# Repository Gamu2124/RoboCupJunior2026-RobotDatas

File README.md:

# AIR - RoboCupJunior2026 RobotData Repository

RoboCupJunior Soccer Lightweight 2026 シーズンにおいて、**ジャパンオープン優勝**、そして世界大会（韓国・仁川）で**競技優勝・総合優勝・コミュニティ賞**を達成したロボット「AIR」の**設計・開発データを公開するリポジトリ**です。

This repository contains the **design, hardware, and software data of AIR**, the **RoboCupJunior Soccer Lightweight 2026 Japan Open Champion and World Championship Champion**.

---
# 概要 / Overview

本リポジトリは、**次世代のRCJコミュニティおよび学生ロボティクスエンジニアへの情報共有**を目的として公開されています。

2026シーズンの開発で使用した**回路設計、組み込みソフトウェア、マルチマイコンによる分散処理システム、3D CADデータ**など、AIRのロボット開発に関する設計データを公開しています。

We open-source **AIR's robot design and development data** to support the global RCJ community and future student roboticists.

The repository includes **custom PCB designs, multi-MCU embedded firmware, and 3D CAD models** used in the development of AIR during the 2026 season.

---

<table align="center">
  <tr>
    <td align="center">
      
      <br>
      <b>Japan Open 2026</b>
    </td>
    <td align="center">
      
      <br>
      <b>World Championship 2026</b>
    </td>
  </tr>
</table>

---

# 大会実績 / Competition Results

* **RoboCupJunior Japan Open 2026**

  * 🥇 **競技 優勝 / 1st Place**

* **RoboCup World Championship 2026**

  * **Incheon, Republic of Korea**
  * 🥇 **競技 優勝 / Individual 1st Place**
  * 🏆 **総合 優勝 / Overall 1st Place**
  * 🏅 **コミュニティ賞 / Community Award**

---

# 技術的ハイライト / Technical Highlights

AIRのシステムは、**高速なセンサ処理と制御、複数のマイコンへの処理分散、そして競技環境での安定動作**を重視して設計されています。

* **Teensy 4.1を中心としたマルチマイコン分散処理**

  メインマイコンとして**Teensy 4.1**を使用し、複数のUARTを介してボール検出、ライン検出、壁面距離計測、UIなどの処理をサブマイコンへ分散しています。

* **24基のTSSP58038による高密度ボール検出**

  **RP2350Aと24個の赤外線センサ**を使用し、複数方向からのボール検出を高速に行います。得られたセンサ情報から**ボールの方向や距離を推定**し、ロボットの走行制御に利用しています。

* **FreeRTOSを用いた非ブロッキング超音波計測**

  **XIAO ESP32-S3上でFreeRTOSを利用**し、超音波センサによる壁面距離計測をメインの制御処理から分離しています。

* **電源・回路の安定性を重視した設計**

  **DCDCコンバータによる電源系統の分離**、大電流を扱うキッカー回路、複数のマイコン・センサ・モータドライバを統合した電源および信号系統を設計しています。

* **世界大会でのリモートシステムへの対応**

  **世界大会で使用された公式リモートシステム**に対応するための通信・制御機能を実装しています。

---

# リポジトリ構成 / Repository Structure

```text
.
├── Circuit/             # 回路・PCB設計データ (KiCad)
├── Hardware/            # 3D CAD・機械設計データ
├── Program/             # 組み込みソフトウェア・プログラム
├── PresentationSheet/   # プレゼンテーション・資料
├── .gitattributes
└── README.md
```

---

# ハードウェア仕様とシステム進化 / Hardware Architecture & Evolution

AIRのハードウェア構成は、**ジャパンオープンから世界大会（Incheon）にかけて大幅に進化**しました。

| ユニット / System              | Japan Open モデル                    | World Championship (Incheon) モデル |
| -------------------------- | --------------------------------- | -------------------------------- |
| **Main MCU**               | Teensy 4.1                        | Teensy 4.1                       |
| **Ball Sub MCU & Sensors** | ATmega32U4 + TSSP4038             | **RP2350A + TSSP58038 × 24**     |
| **Line Sub MCU & Sensors** | ATmega2560 + B19H1LS / LM393      | **RP2350B + B19H1LS / LM393**    |
| **Wall / US MCU**          | XIAO ESP32-S3                     | XIAO ESP32-S3                    |
| **UI & Remote Control**    | ESP32 WROOM-32E + OLED + NeoPixel | **XIAO ESP32-S3 + OLED**         |
| **Motor Driver**           | DRV8432                           | **DRV8432**                      |
| **Kicker System**          | CB1037 + Pch/Nch MOSFET           | **CB1037 + AQW212 + XL6009**     |
| **Power Distribution**     | LM2576系電源                         | **AP64500SP系電源**                 |

---

# ソフトウェア機能 / Software Architecture

主に**C/C++およびPython**を用いて開発された、**マルチマイコン分散処理によるロボット制御システム**です。

* **Ball Tracking**

  **24個のTSSP58038**から得られるセンサ情報をRP2350Aで高速処理し、**ボールの方向および距離を推定**します。

* **Line Keep**

  **B19H1LSおよびLM393**を使用したラインセンサシステムにより、フィールド上の白線を検出し、フィールド外への逸脱を防止します。

* **Wall Distance**

  ESP32-S3上で**FreeRTOS**を利用し、超音波センサによる壁面距離計測をバックグラウンドで実行します。

* **Motion Control**

  **IMU（BNO055）から得られる姿勢情報を利用したPIDベースの全方向移動制御**を行います。

* **Strategy State Machine**

  ボール検出、ライン検出、壁面距離、ロボットの状態などの情報をもとに、**試合中の動作を状態機械として制御**します。

* **World Championship Remote Control**

  **世界大会で使用された公式リモートシステムに対応した通信・制御機能**を実装しています。

---

# 開発環境・使用設備 / Development Environment & Equipment

### Software Tools

* **3D CAD**: Autodesk Fusion 360
* **EDA (PCB Design)**: KiCad
* **IDE / Programming**: Visual Studio Code / MaixPy IDE
* **Presentation & Media**: Canva

### Hardware & Manufacturing Equipment

* **3D Printers**: Bambu Lab A1 mini / Bambu Lab P1S / Flashforge Adventurer 5M
* **PCB Fabrication**: JLCPCB
* **Machining / Tools**: 小型CNC加工機

---

# CAD設計データ / CAD Models

AIRを構成する**カスタム機械部品をAutodesk Fusion 360で設計**しています。

主な設計データには以下が含まれます。

* **シャーシ構造** / Chassis
* **キッカーユニット** / Kicker Unit
* **センサマウント各種** / Sensor Mounts
* **オムニホイールモジュール** / Omni Wheel Modules
* **ドリブラー機構** / Dribbler Mechanism

---

# 公開基板データ / PCB Designs

ロボットに使用した**自作基板のKiCad設計データ**を公開しています。

## 日本大会機

1. **メイン基板 (`main_unit`)**
   各種マイコン・センサ・制御系を統合したメイン基板

2. **ボールセンサー基板 (`ball_unit`)**
   **TSSP4038およびATmega32U4**を搭載したボール検出基板

3. **ラインセンサー基板 (`line_unit`)**
   **B19H1LS、LM393、ATmega2560**を搭載したライン検出基板

4. **電源基板 (`power_unit`)**
   **LM2576**を使用した電源基板

5. **モータドライバ基板 (`md_unit`)**
   **DRV8432**を使用したモータドライバ基板

6. **キッカー制御基板 (`kicker_unit`)**
   キッカー用の**大電流スイッチング・絶縁回路**

## 世界大会機

1. **メイン基板 (`main_unit`)**
   各種マイコン・IMU・UIなどを統合したメイン基板

2. **ボールセンサー基板 (`ball_unit`)**
   **TSSP58038 × 24およびRP2350A**を搭載した高密度ボール検出基板

3. **ラインセンサー基板 (`line_unit`)**
   **B19H1LS、LM393、RP2350B**を搭載したライン検出基板

4. **電源基板 (`power_unit`)**
   **AP64500SP**を使用した電源基板

5. **モータドライバ基板 (`md_unit`)**
   **DRV8432**を使用したモータドライバ基板

6. **キッカー制御基板 (`kicker_unit`)**
   **昇圧回路、大電流スイッチング回路、AQW212**を使用したキッカー制御基板

---

# スポンサー / Sponsors

本プロジェクトの活動を支援していただいたスポンサー・団体の皆様に、心より感謝申し上げます。

* **JLCPCB**
  https://jlcpcb.com/

* **DigiKey**
  https://www.digikey.jp/

* **株式会社人機一体**
  https://www.jinki.jp/

* **MAXON**
  https://maxonjapan.com/

* **タカハ機工株式会社**
  https://www.takaha.co.jp/

* **株式会社システムアイインターナショナル**
  https://www.systemi.com/

* **ライフ&キャリアコンサルティング LACIQUE**
  https://www.lacique.com/

* **医療法人社団 翠会 水口病院**
  https://www.minakuchi-hp.or.jp/

* **JOJISTABLE**
  https://x.com/JojiStable

* **立命館守山高校 & 立命館大学**
  https://www.mrc.ritsumei.ac.jp/
  https://www.ritsumei.ac.jp/

---

# チーム情報・お問い合わせ / Team Information & Contact

## AIR

**RoboCupJunior Soccer Lightweight & Infrared Team from Japan**

**World Champion 2026**

### チーム実績 / Team History

* **2025 シーズン**

  * RoboCupJunior Japan Open 2025 🥉 **3位**
  * RoboCup World Championship 2025
    Salvador, Brazil 🥉 **Individual 3rd Place**

* **2026 シーズン**

  * RoboCupJunior Japan Open 2026 🥇 **優勝**
  * RoboCup World Championship 2026
    Incheon, Republic of Korea 🏆 **Individual 1st Place**
  * 🏅 **Community Award**

---

### お問い合わせ・ご質問 / Contact Information

本リポジトリの内容、設計データ、その他技術的なご質問やお問い合わせについては、以下よりご連絡ください。

* **X (Twitter) DM**: [@Air_Gamu_rcj](https://x.com/Air_Gamu_rcj)

* **Email**: [airkorea2026@gmail.com](mailto:airkorea2026@gmail.com)

### 公式メディア・SNS / Links

* **X (Twitter)**: [@Air_3838](https://x.com/Air_3838)

* **YouTube**: [AIR-RCJ Channel](https://www.youtube.com/@AIR-RCJ)

* **note**: [AIR Official note](https://note.com/air_rcj)

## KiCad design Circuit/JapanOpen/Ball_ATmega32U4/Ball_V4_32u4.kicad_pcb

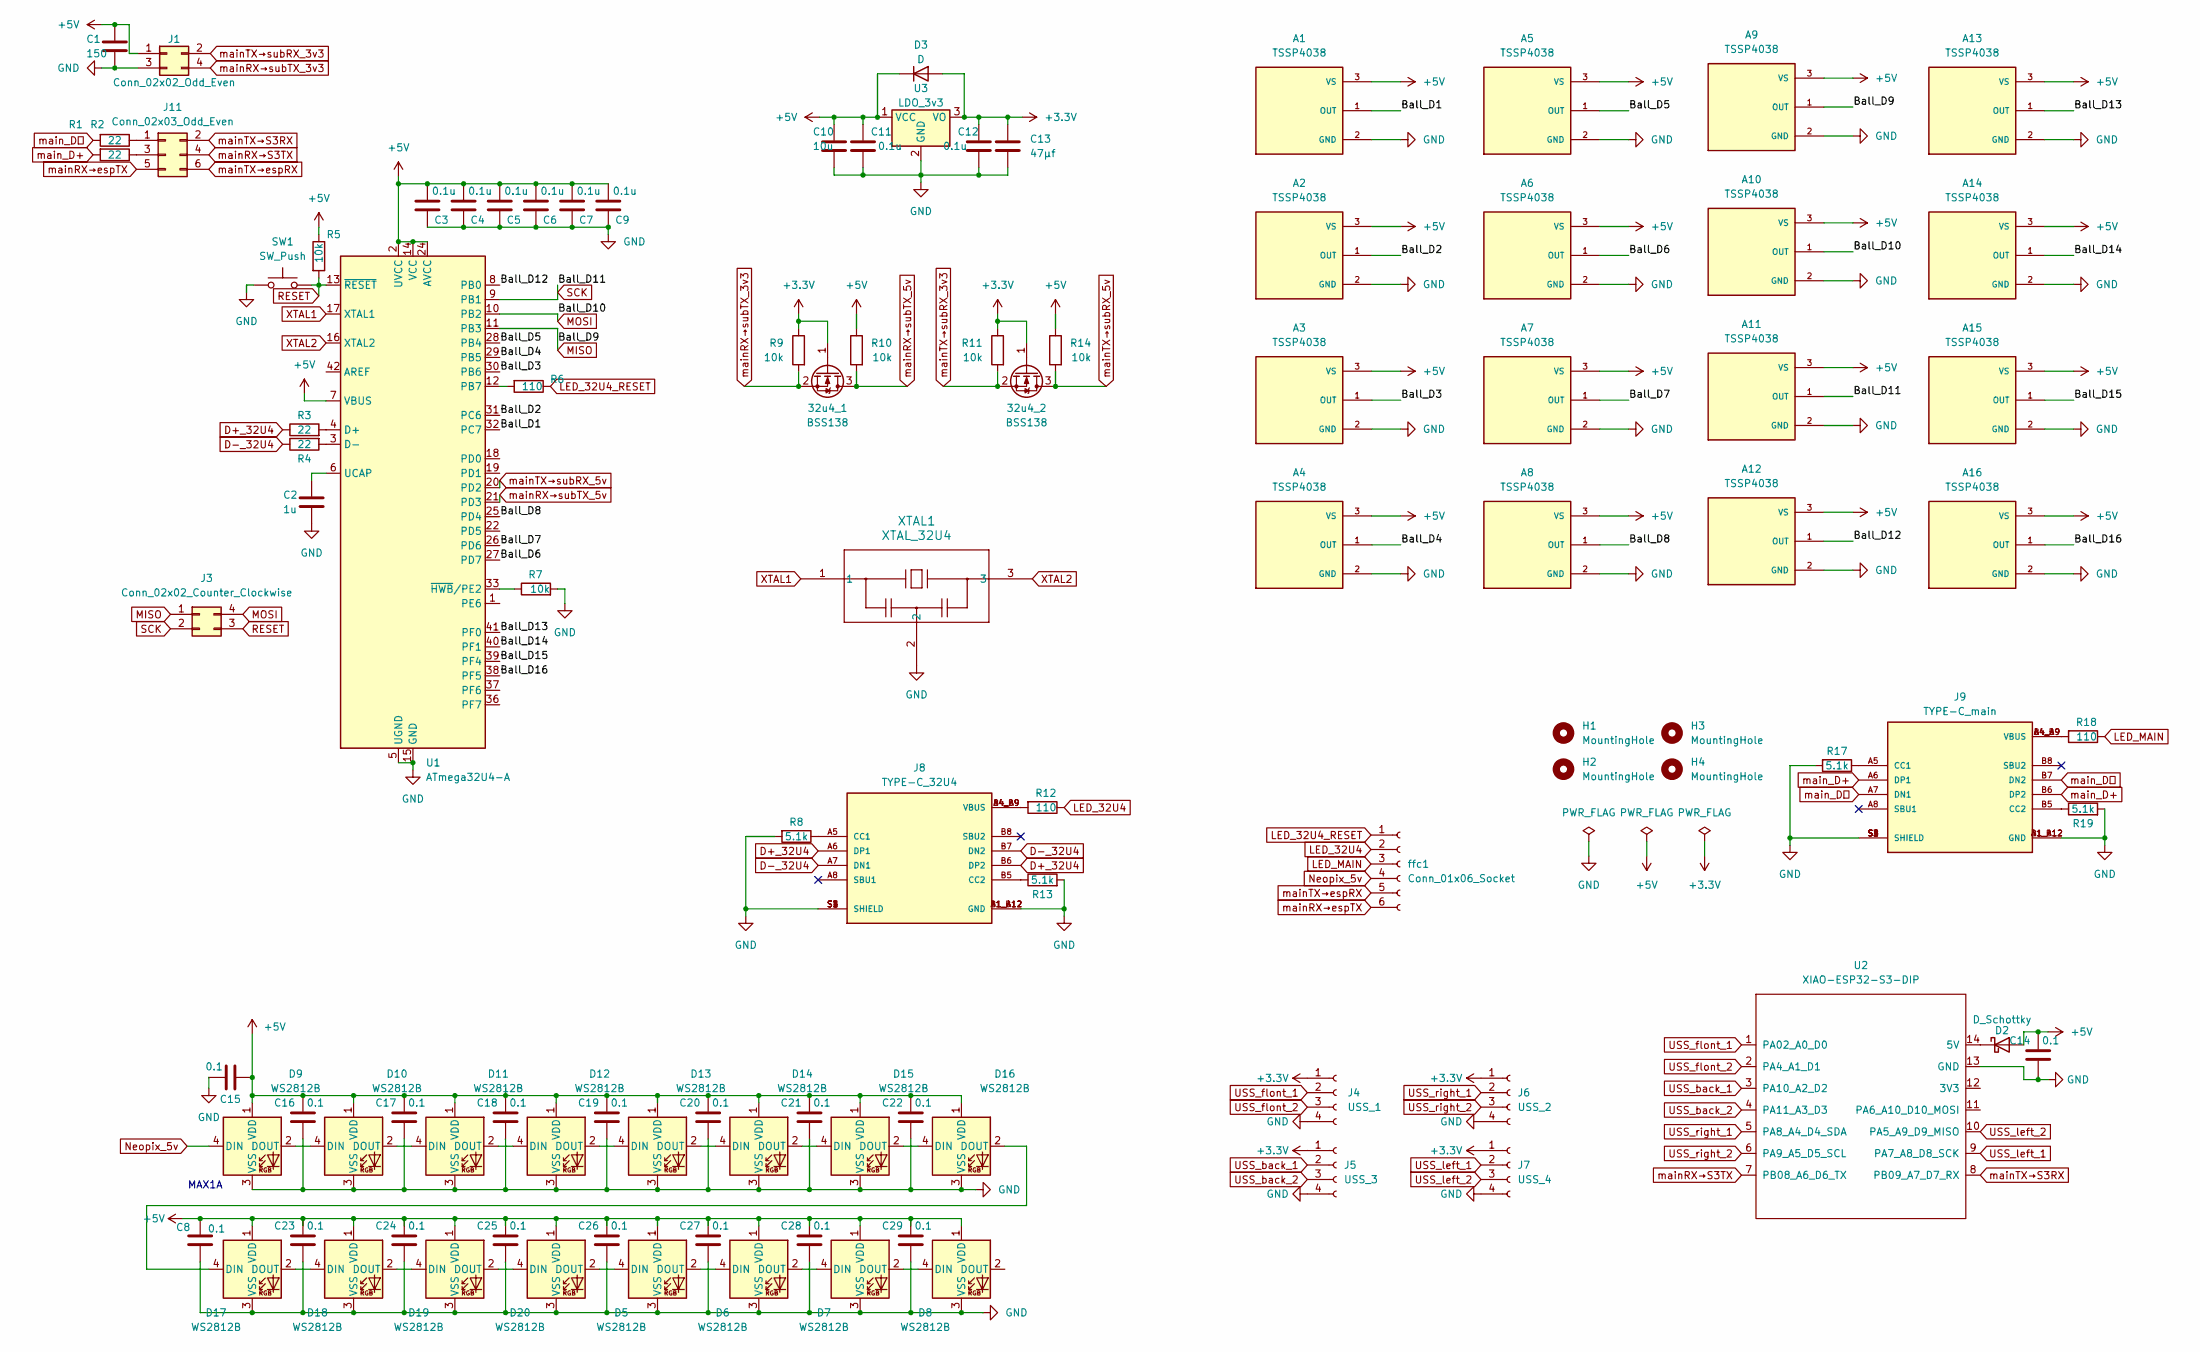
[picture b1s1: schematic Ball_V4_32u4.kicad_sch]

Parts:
32u4_1, 32u4_2: BSS138; SOT-23; LCSC C192057
A1, A2, A3, A4, A5, A6, A7, A8, A9, A10, A11, A12, A13, A14, A15, A16: TSSP4038; XDCR_TSSP4038; PARTREV 2.3
C1: 150; CP_Radial_D5.0mm_P2.50mm; LCSC C59923
C2: 1u; C_1206_3216Metric; LCSC C1848
C3, C4, C5, C6, C7, C9, C11, C12: 0.1u; C_0603_1608Metric_Pad1.08x0.95mm_HandSolder; LCSC C1581
C8, C14, C16, C17, C18, C19, C20, C21, C22, C23, C24, C25, C26, C27, C28, C29: 0.1; C_0603_1608Metric_Pad1.08x0.95mm_HandSolder; LCSC C1581
C10: 10u; C_0805_2012Metric; LCSC C1713
C13: 47μf; CP_Radial_D5.0mm_P2.00mm
C15: 0.1; C_0603_1608Metric_Pad1.08x0.95mm_HandSolder; LCSC C1848
D2: D_Schottky; D_A-405_P10.16mm_Horizontal
D3: D; D_SOD-123F
D5, D6, D7, D8, D9, D10, D11, D12, D13, D14, D15, D16, D17, D18, D19, D20: WS2812B; LED_WS2812B_PLCC4_5.0x5.0mm_P3.2mm
H1, H2, H3, H4: MountingHole; MountingHole_3.2mm_M3
J1: Conn_02x02_Odd_Even; PinHeader_2x02_P2.54mm_Vertical
J3: Conn_02x02_Counter_Clockwise; PinHeader_2x02_P2.54mm_Vertical
J4: USS_1; PinSocket_1x04_P2.54mm_Vertical
J5: USS_3; PinSocket_1x04_P2.54mm_Vertical
J6: USS_2; PinSocket_1x04_P2.54mm_Vertical
J7: USS_4; PinSocket_1x04_P2.54mm_Vertical
J8: TYPE-C_32U4; NELTRON_5077CR-16SMC2-BK-TR; PARTREV B
J9: TYPE-C_main; NELTRON_5077CR-16SMC2-BK-TR; PARTREV B
J11: Conn_02x03_Odd_Even; PinSocket_2x03_P2.54mm_Vertical
R1, R2, R3, R4: 22; R_1206_3216Metric; LCSC C17958
R5, R7, R9, R10, R11, R14: 10k; R_1206_3216Metric; LCSC C1489
R6, R12, R18: 110; R_1206_3216Metric; LCSC C17909
R8, R13, R17, R19: 5.1k; R_0603_1608Metric_Pad0.98x0.95mm_HandSolder; LCSC C26033
SW1: SW_Push; Switch_SKRPABE010
U1: ATmega32U4-A; TQFP-44_10x10mm_P0.8mm; LCSC C44854
U2: XIAO-ESP32-S3-DIP; XIAO-ESP32-S3-SMD
U3: LDO_3v3; TO-252-2
XTAL1: XTAL_32U4; CSTNE16M0V530000R0_MUR
ffc1: Conn_01x06_Socket; TE_84952-6_1x06-1MP_P1.0mm_Horizontal

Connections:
+3.3V: 32u4_1.1 (G), 32u4_2.1 (G), C12.1, C13.1, D3.2 (A), J4.1, J5.1, J6.1, J7.1, R9.1, R11.1, U3.3 (VO)
+5V: A1.3 (VS), A2.3 (VS), A3.3 (VS), A4.3 (VS), A5.3 (VS), A6.3 (VS), A7.3 (VS), A8.3 (VS), A9.3 (VS), A10.3 (VS), A11.3 (VS), A12.3 (VS), A13.3 (VS), A14.3 (VS), A15.3 (VS), A16.3 (VS), C1.1, C3.2, C4.2, C5.2, C6.2, C7.2, C8.2, C9.2, C10.1, C11.1, C14.2, C15.2, C16.2, C17.2, C18.2, C19.2, C20.2, C21.2, C22.2, C23.2, C24.2, C25.2, C26.2, C27.2, C28.2, C29.2, D2.2 (A), D3.1 (K), D5.1 (VDD), D6.1 (VDD), D7.1 (VDD), D8.1 (VDD), D9.1 (VDD), D10.1 (VDD), D11.1 (VDD), D12.1 (VDD), D13.1 (VDD), D14.1 (VDD), D15.1 (VDD), D16.1 (VDD), D17.1 (VDD), D18.1 (VDD), D19.1 (VDD), D20.1 (VDD), J1.1, R5.1, R10.1, R14.1, U1.2 (UVCC), U1.7 (VBUS), U1.14 (VCC), U1.24 (AVCC), U1.34 (VCC), U1.44 (AVCC), U3.1 (VCC)
/Ball_D1: A1.1 (OUT), U1.32 (PC7)
/Ball_D2: A2.1 (OUT), U1.31 (PC6)
/Ball_D3: A3.1 (OUT), U1.30 (PB6)
/Ball_D4: A4.1 (OUT), U1.29 (PB5)
/Ball_D5: A5.1 (OUT), U1.28 (PB4)
/Ball_D6: A6.1 (OUT), U1.27 (PD7)
/Ball_D7: A7.1 (OUT), U1.26 (PD6)
/Ball_D8: A8.1 (OUT), U1.25 (PD4)
/Ball_D12: A12.1 (OUT), U1.8 (PB0)
/Ball_D13: A13.1 (OUT), U1.41 (PF0)
/Ball_D14: A14.1 (OUT), U1.40 (PF1)
/Ball_D15: A15.1 (OUT), U1.39 (PF4)
/Ball_D16: A16.1 (OUT), U1.38 (PF5)
D+_32U4: J8.A6 (DP1), J8.B6 (DP2), R3.1
D-_32U4: J8.A7 (DN1), J8.B7 (DN2), R4.1
GND: A1.2 (GND), A2.2 (GND), A3.2 (GND), A4.2 (GND), A5.2 (GND), A6.2 (GND), A7.2 (GND), A8.2 (GND), A9.2 (GND), A10.2 (GND), A11.2 (GND), A12.2 (GND), A13.2 (GND), A14.2 (GND), A15.2 (GND), A16.2 (GND), C1.2, C2.2, C3.1, C4.1, C5.1, C6.1, C7.1, C8.1, C9.1, C10.2, C11.2, C12.2, C13.2, C14.1, C15.1, C16.1, C17.1, C18.1, C19.1, C20.1, C21.1, C22.1, C23.1, C24.1, C25.1, C26.1, C27.1, C28.1, C29.1, D5.3 (VSS), D6.3 (VSS), D7.3 (VSS), D8.3 (VSS), D9.3 (VSS), D10.3 (VSS), D11.3 (VSS), D12.3 (VSS), D13.3 (VSS), D14.3 (VSS), D15.3 (VSS), D16.3 (VSS), D17.3 (VSS), D18.3 (VSS), D19.3 (VSS), D20.3 (VSS), J1.3, J4.4, J5.4, J6.4, J7.4, J8.A1_B12 (GND), J8.B1_A12 (GND), J8.S1 (SHIELD), J8.S2 (SHIELD), J8.S3 (SHIELD), J8.S4 (SHIELD), J9.A1_B12 (GND), J9.B1_A12 (GND), J9.S1 (SHIELD), J9.S2 (SHIELD), J9.S3 (SHIELD), J9.S4 (SHIELD), R7.2, R8.2, R13.2, R17.2, R19.2, SW1.2, U1.5 (UGND), U1.15 (GND), U1.23 (GND), U1.35 (GND), U1.43 (GND), U2.13 (GND), U3.2 (GND), XTAL1.2
LED_32U4: R12.1, ffc1.2
LED_32U4_RESET: R6.1, ffc1.1
LED_MAIN: R18.1, ffc1.3
MISO: A9.1 (OUT), J3.1, U1.11 (PB3)
MOSI: A10.1 (OUT), J3.4, U1.10 (PB2)
Neopix_5v: D9.4 (DIN), ffc1.4
unnamed: D2.1 (K), U2.14 (5V)
unnamed: D5.2 (DOUT), D6.4 (DIN)
unnamed: D6.2 (DOUT), D7.4 (DIN)
unnamed: D7.2 (DOUT), D8.4 (DIN)
unnamed: D9.2 (DOUT), D10.4 (DIN)
unnamed: D10.2 (DOUT), D11.4 (DIN)
unnamed: D11.2 (DOUT), D12.4 (DIN)
unnamed: D12.2 (DOUT), D13.4 (DIN)
unnamed: D13.2 (DOUT), D14.4 (DIN)
unnamed: D14.2 (DOUT), D15.4 (DIN)
unnamed: D15.2 (DOUT), D16.4 (DIN)
unnamed: D16.2 (DOUT), D17.4 (DIN)
unnamed: D17.2 (DOUT), D18.4 (DIN)
unnamed: D18.2 (DOUT), D19.4 (DIN)
unnamed: D19.2 (DOUT), D20.4 (DIN)
unnamed: D5.4 (DIN), D20.2 (DOUT)
unnamed: J8.A5 (CC1), R8.1
unnamed: J8.B5 (CC2), R13.1
unnamed: J8.A4_B9 (VBUS), J8.B4_A9 (VBUS), R12.2
unnamed: J9.A5 (CC1), R17.1
unnamed: J9.B5 (CC2), R19.1
unnamed: J9.A4_B9 (VBUS), J9.B4_A9 (VBUS), R18.2
unnamed: J11.1, R1.1
unnamed: J11.3, R2.1
unnamed: R3.2, U1.4 (D+)
unnamed: R4.2, U1.3 (D-)
unnamed: R6.2, U1.12 (PB7)
unnamed: C2.1, U1.6 (UCAP)
unnamed: R7.1, U1.33 (~HWB/PE2)
RESET: J3.3, R5.2, SW1.1, U1.13 (~RESET)
SCK: A11.1 (OUT), J3.2, U1.9 (PB1)
USS_back_1: J5.2, U2.3 (PA10_A2_D2)
USS_back_2: J5.3, U2.4 (PA11_A3_D3)
USS_flont_1: J4.2, U2.1 (PA02_A0_D0)
USS_flont_2: J4.3, U2.2 (PA4_A1_D1)
USS_left_1: J7.2, U2.9 (PA7_A8_D8_SCK)
USS_left_2: J7.3, U2.10 (PA5_A9_D9_MISO)
USS_right_1: J6.2, U2.5 (PA8_A4_D4_SDA)
USS_right_2: J6.3, U2.6 (PA9_A5_D5_SCL)
XTAL1: U1.17 (XTAL1), XTAL1.1
XTAL2: U1.16 (XTAL2), XTAL1.3
mainRX→S3TX: J11.4, U2.7 (PB08_A6_D6_TX)
mainRX→espTX: J11.5, ffc1.6
mainRX→subTX_3v3: 32u4_1.2 (S), J1.4, R9.2
mainRX→subTX_5v: 32u4_1.3 (D), R10.2, U1.21 (PD3)
mainTX→S3RX: J11.2, U2.8 (PB09_A7_D7_RX)
mainTX→espRX: J11.6, ffc1.5
mainTX→subRX_3v3: 32u4_2.2 (S), J1.2, R11.2
mainTX→subRX_5v: 32u4_2.3 (D), R14.2, U1.20 (PD2)
main_D+: J9.A6 (DP1), J9.B6 (DP2), R2.2
main_Dー: J9.A7 (DN1), J9.B7 (DN2), R1.2

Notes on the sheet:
MAX1A

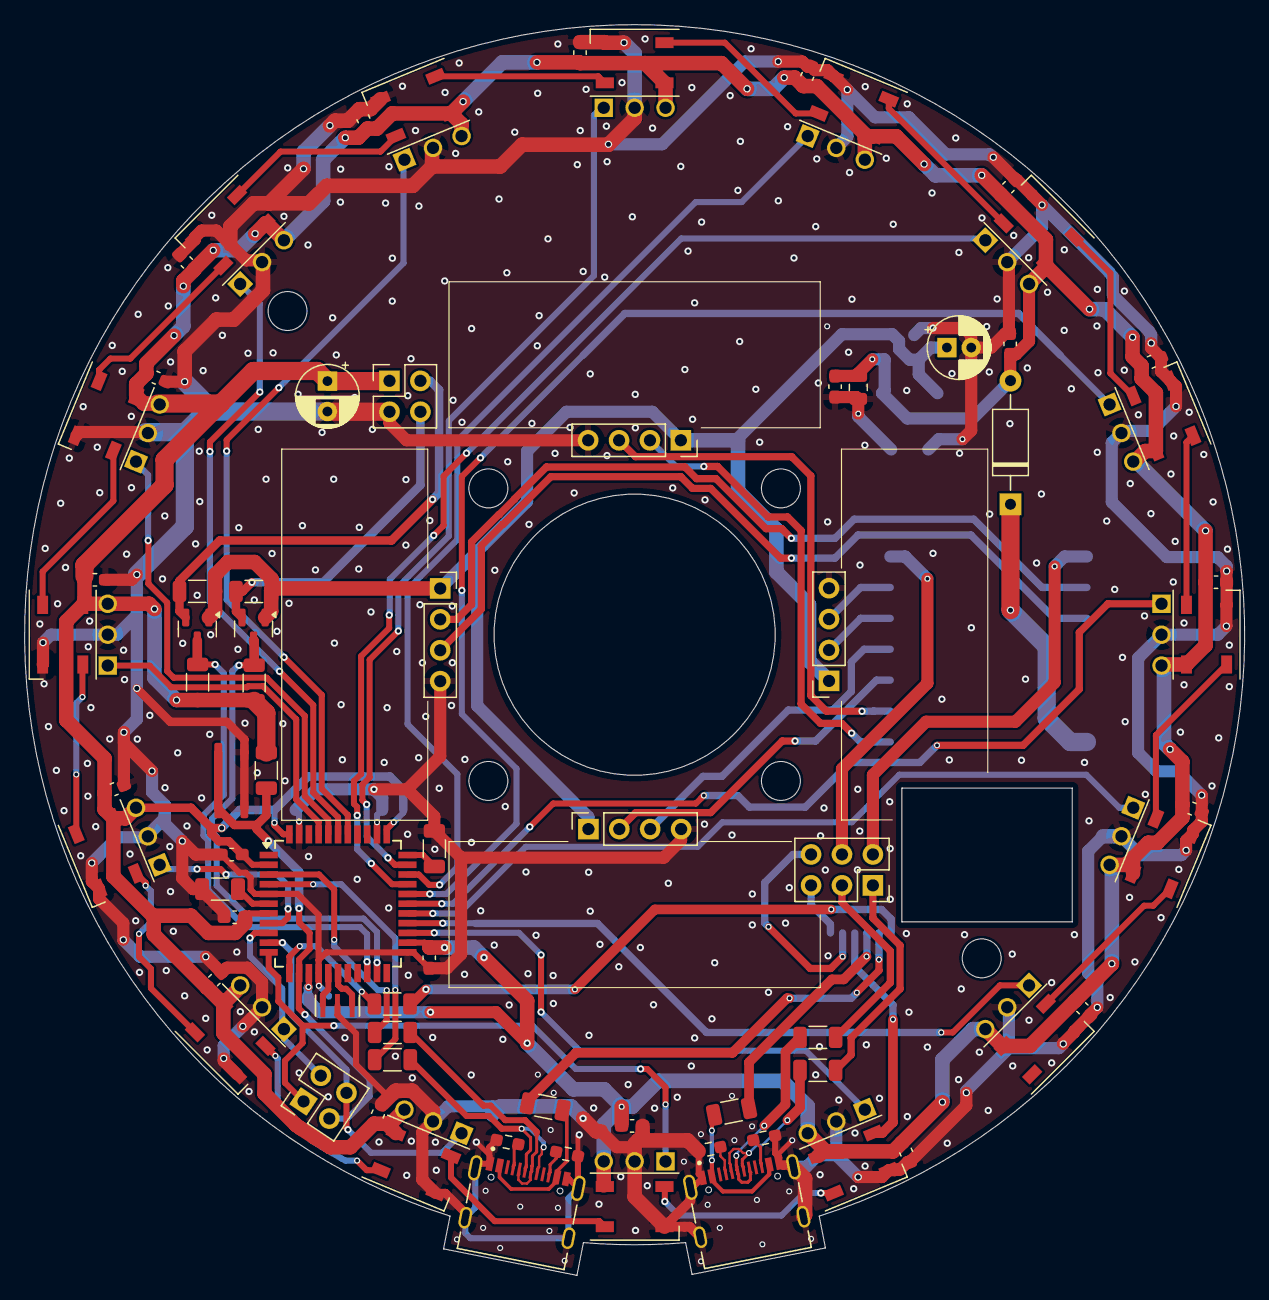
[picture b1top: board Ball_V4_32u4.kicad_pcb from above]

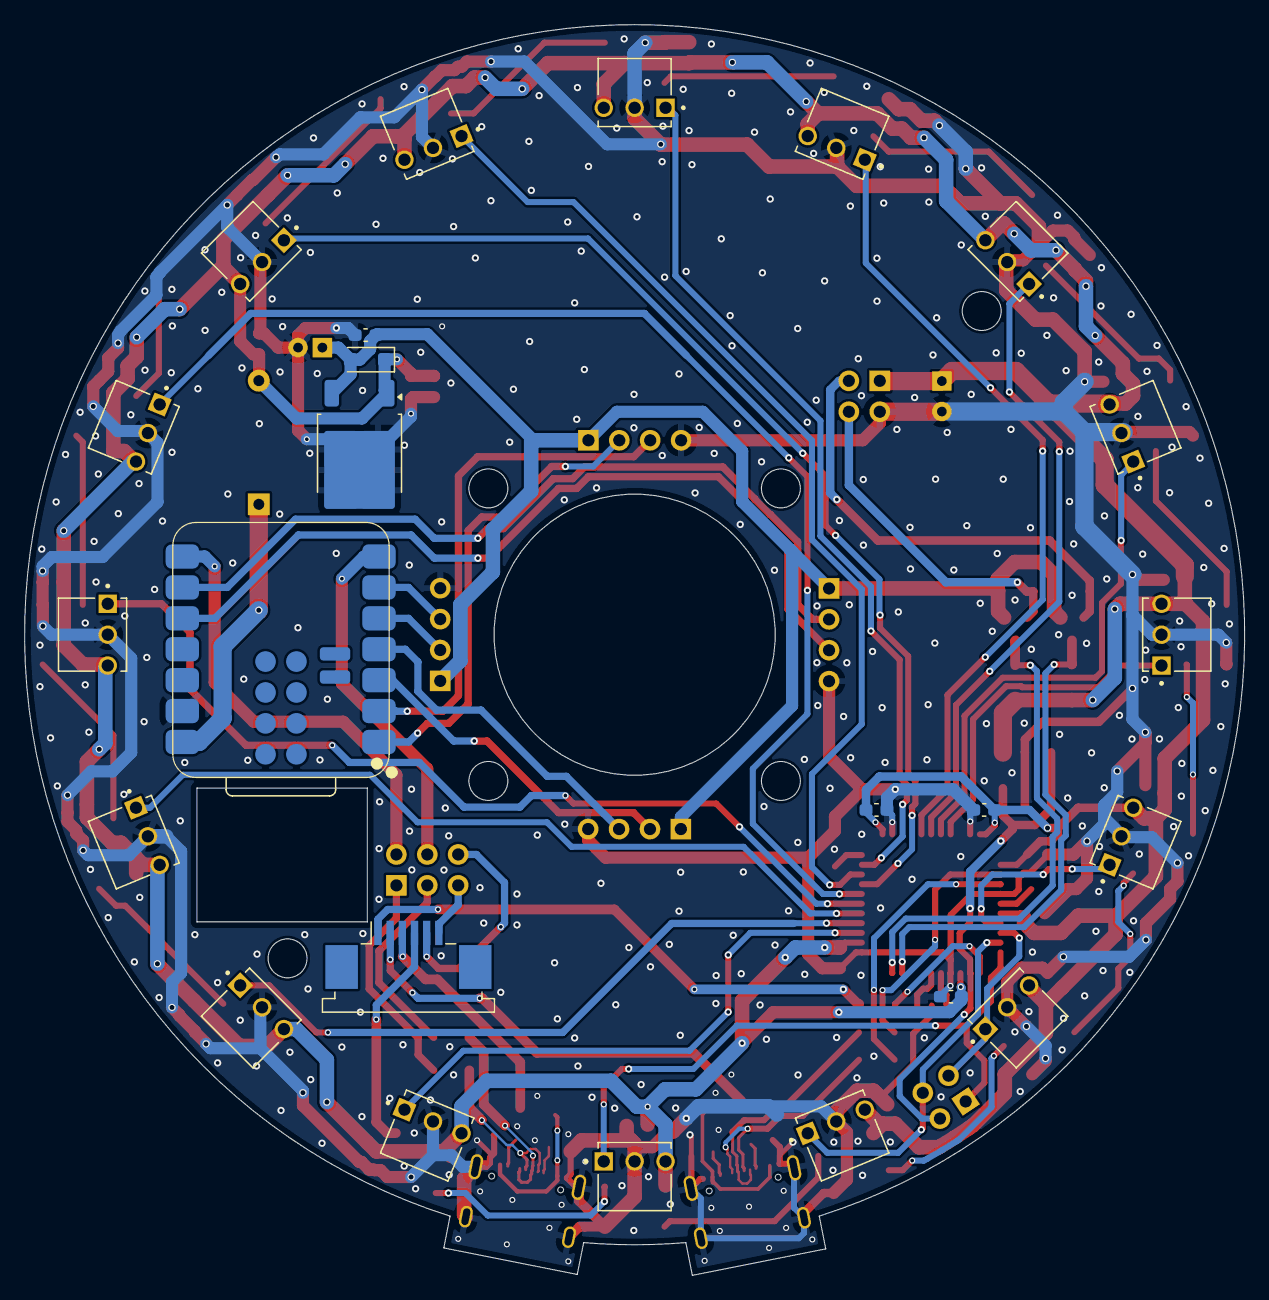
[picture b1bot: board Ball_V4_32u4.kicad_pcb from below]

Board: 2 copper layers, 100.3 x 102.8 mm, 103 parts (24 on the bottom side), 75 nets.

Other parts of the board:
H5, H5#2: MountingHole; MountingHole_3.2mm_M3

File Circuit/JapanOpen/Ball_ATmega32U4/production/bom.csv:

Designator,Footprint,Quantity,Value,LCSC Part #
"32U4_1, 32U4_2",SOT-23,2,BSS138, C192057
"A1, A10, A11, A12, A13, A14, A15, A16, A2, A3, A4, A5, A6, A7, A8, A9",XDCR_TSSP4038,16,TSSP4038,
C1,CP_Radial_D5.0mm_P2.50mm,1,150,C59923
C10,0805,1,10u, C1713
"C11, C12, C3, C4, C5, C6, C7, C9",0603,8,0.1u,C1581
C13,CP_Radial_D5.0mm_P2.00mm,1,47μf,
"C14, C16, C17, C18, C19, C20, C21, C22, C23, C24, C25, C26, C27, C28, C29, C8",0603,16,0.1,C1581
C15,0603,1,0.1,C1848 
C2,1206,1,1u,C1848 
"D10, D11, D12, D13, D14, D15, D16, D17, D18, D19, D20, D5, D6, D7, D8, D9",LED_WS2812B_PLCC4_5.0x5.0mm_P3.2mm,16,WS2812B,
D2,D_A-405_P10.16mm_Horizontal,1,D_Schottky,
D3,D_SOD-123F,1,D,
FFC1,TE_84952-6_1x06-1MP_P1.0mm_Horizontal,1,Conn_01x06_Socket,
J1,PinHeader_2x02_P2.54mm_Vertical,1,Conn_02x02_Odd_Even,
J11,PinSocket_2x03_P2.54mm_Vertical,1,Conn_02x03_Odd_Even,
J3,PinHeader_2x02_P2.54mm_Vertical,1,Conn_02x02_Counter_Clockwise,
J4,PinSocket_1x04_P2.54mm_Vertical,1,USS_1,
J5,PinSocket_1x04_P2.54mm_Vertical,1,USS_3,
J6,PinSocket_1x04_P2.54mm_Vertical,1,USS_2,
J7,PinSocket_1x04_P2.54mm_Vertical,1,USS_4,
J8,NELTRON_5077CR-16SMC2-BK-TR,1,TYPE-C_32U4,
J9,NELTRON_5077CR-16SMC2-BK-TR,1,TYPE-C_main,
"R1, R2, R3, R4",1206,4,22,C17958 
"R10, R11, R14, R9",1206,4,10k, C1489
"R12, R18, R6",1206,3,110,C17909
"R13, R17, R19, R8",0603,4,5.1k,C26033
"R5, R7",1206,2,10k,C1489
SW1,Switch_SKRPABE010,1,SW_Push,
U1,TQFP-44_10x10mm_P0.8mm,1,ATmega32U4-A, C44854
U2,XIAO-ESP32-S3-SMD,1,XIAO-ESP32-S3-DIP,
U3,TO-252-2,1,LDO_3v3,
XTAL1,CSTNE16M0V530000R0_MUR,1,XTAL_32U4,

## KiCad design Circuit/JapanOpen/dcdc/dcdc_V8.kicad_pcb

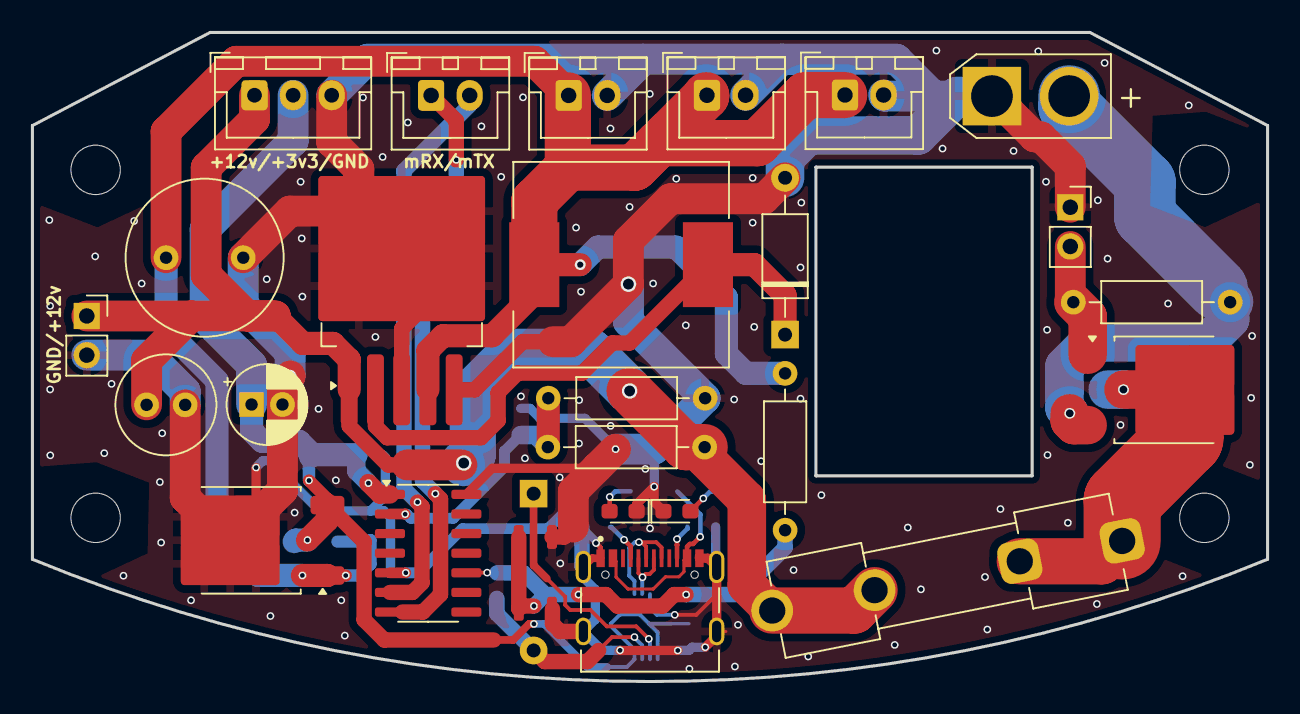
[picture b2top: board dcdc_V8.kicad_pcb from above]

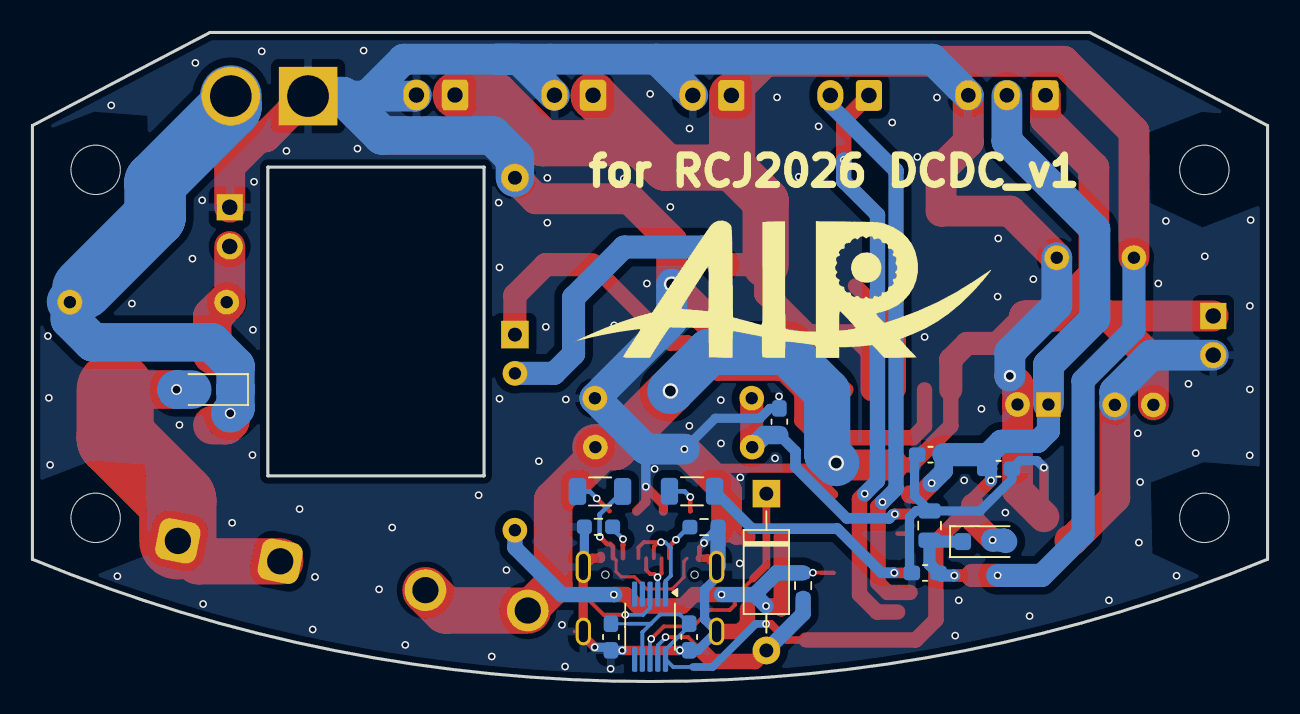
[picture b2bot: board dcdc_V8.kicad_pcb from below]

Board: 2 copper layers, 80.0 x 42.0 mm, 46 parts (16 on the bottom side), 22 nets.

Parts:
C1: 100u; C_Radial_D6.3mm_H5.0mm_P2.50mm
C2: 1000u; C_Radial_D10.0mm_H12.5mm_P5.00mm
C3, C4, C5, C8: 0.1; C_0603_1608Metric_Pad1.08x0.95mm_HandSolder
C9: 10u; C_0805_2012Metric
C10, C11: 0.1u; C_0603_1608Metric_Pad1.08x0.95mm_HandSolder
C12: 47u; CP_Radial_D5.0mm_P2.00mm
D1, D2: D; D_SOD-123F
D3: RED; LED_0603_1608Metric_Pad1.05x0.95mm_HandSolder
D5: GREEN; LED_0603_1608Metric_Pad1.05x0.95mm_HandSolder
F1: Fuse; Fuseholder_Clip-5x20mm_Keystone_3517_Inline_P23.11x6.76mm_D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
H3, H3#2, H4, H4#2: MountingHole; MountingHole_3.2mm_M3
J1: TYPE-C_ESP32; NELTRON_5077CR-16SMC2-BK-TR
L1: 100u; L_Sunlord_MWSA1204S-1R0
LiPo_1: XT30_IN; AMASS_XT30U-M_1x02_P5.0mm_Vertical
Line_1: Conn_01x02_Socket; JST_XH_B2B-XH-A_1x02_P2.50mm_Vertical
MDR_1: Conn_01x03_Socket; JST_XH_B3B-XH-A_1x03_P2.50mm_Vertical
OLED_1: Conn_01x02_Socket; PinSocket_1x02_P2.54mm_Vertical
Q1: PMOS; TO-252-2
R1, R2, R5: 10k; R_Axial_DIN0207_L6.3mm_D2.5mm_P10.16mm_Horizontal
R3: 4.7k; R_0603_1608Metric
R4: 3.3k; R_Axial_DIN0207_L6.3mm_D2.5mm_P10.16mm_Horizontal
R6, R9: 5.1k; R_0603_1608Metric_Pad0.98x0.95mm_HandSolder
R7: 110; R_1206_3216Metric
R8: 56; R_1206_3216Metric
SBD1: D; D_A-405_P10.16mm_Horizontal
SBD2: SBD; D_A-405_P10.16mm_Horizontal
SW1: SW_SPST; PinSocket_1x02_P2.54mm_Vertical
SW2: SW_Push; Switch_SKRPABE010
U1: LM2576SX-5.0_NOPB; TO-263-5_TabPin6
U2: CH340E; MSOP-10_3x3mm_P0.5mm
U3: LDO_3v3; TO-252-2
U4: ATtiny814-SS; SOIC-14_3.9x8.7mm_P1.27mm
UI_1: Conn_01x02_Socket; JST_XH_B2B-XH-A_1x02_P2.50mm_Vertical
main_psu1: Conn_01x02_Socket; JST_XH_B2B-XH-A_1x02_P2.50mm_Vertical
main_uart1: Conn_01x02_Socket; JST_XH_B2B-XH-A_1x02_P2.50mm_Vertical

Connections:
+3.3V: C3.1, C4.2, C5.2, C11.1, C12.1, D2.2 (A), MDR_1.2, U2.7 (VCC), U2.10 (V3), U3.3 (VO), U4.1 (VCC)
+5V: C2.1, C9.1, C10.1, D2.1 (K), L1.2, Line_1.1, R2.1, U1.4 (FB), U3.1 (VCC), UI_1.1, main_psu1.1
D+: J1.A6 (DP1), J1.B6 (DP2), U2.1 (UD+)
D-: J1.A7 (DN1), J1.B7 (DN2), U2.2 (UD-)
GND: C1.2, C2.2, C3.2, C4.1, C5.1, C8.2, C9.2, C10.2, C11.2, C12.2, D3.1 (K), D5.1 (K), J1.A1_B12 (GND), J1.B1_A12 (GND), J1.S1 (SHIELD), J1.S2 (SHIELD), J1.S3 (SHIELD), J1.S4 (SHIELD), LiPo_1.1 (-), Line_1.2, MDR_1.3, OLED_1.2, R4.2, R6.2, R9.2, SBD1.2 (A), SW1.1 (A), SW2.2, U1.3 (GND), U1.5 (ON/OFF), U1.6 (GND__1), U2.3 (GND), U3.2 (GND), U4.14 (GND), UI_1.2, main_psu1.2
unnamed: D1.2 (A), F1.1, Q1.2 (D)
unnamed: D1.1 (K), LiPo_1.2 (+), Q1.3 (S), R1.1
unnamed: D3.2 (A), R7.1
unnamed: D5.2 (A), R8.1
unnamed: J1.A5 (CC1), R6.1
unnamed: J1.B5 (CC2), R9.1
unnamed: J1.A4_B9 (VBUS), J1.B4_A9 (VBUS), R7.2
unnamed: Q1.1 (G), R1.2, SW1.2 (B)
unnamed: L1.1, SBD1.1 (K), U1.2 (OUT)
unnamed: R3.2, SBD2.2 (A), U2.9 (RXD)
unnamed: SBD2.1 (K), U2.8 (TXD)
unnamed: R8.2, U4.5 (PA7)
UPDI: R2.2, R3.1, SW2.1, U4.10 (~RESET/PA0)
VCC: C1.1, F1.2, MDR_1.1, OLED_1.1, R5.1, U1.1 (VIN)
VOUT: C8.1, R4.1, R5.2, U4.2 (PA4)
mainRX→subTX: U4.7 (PB2), main_uart1.1
mainTX→subRX: U4.6 (PB3), main_uart1.2

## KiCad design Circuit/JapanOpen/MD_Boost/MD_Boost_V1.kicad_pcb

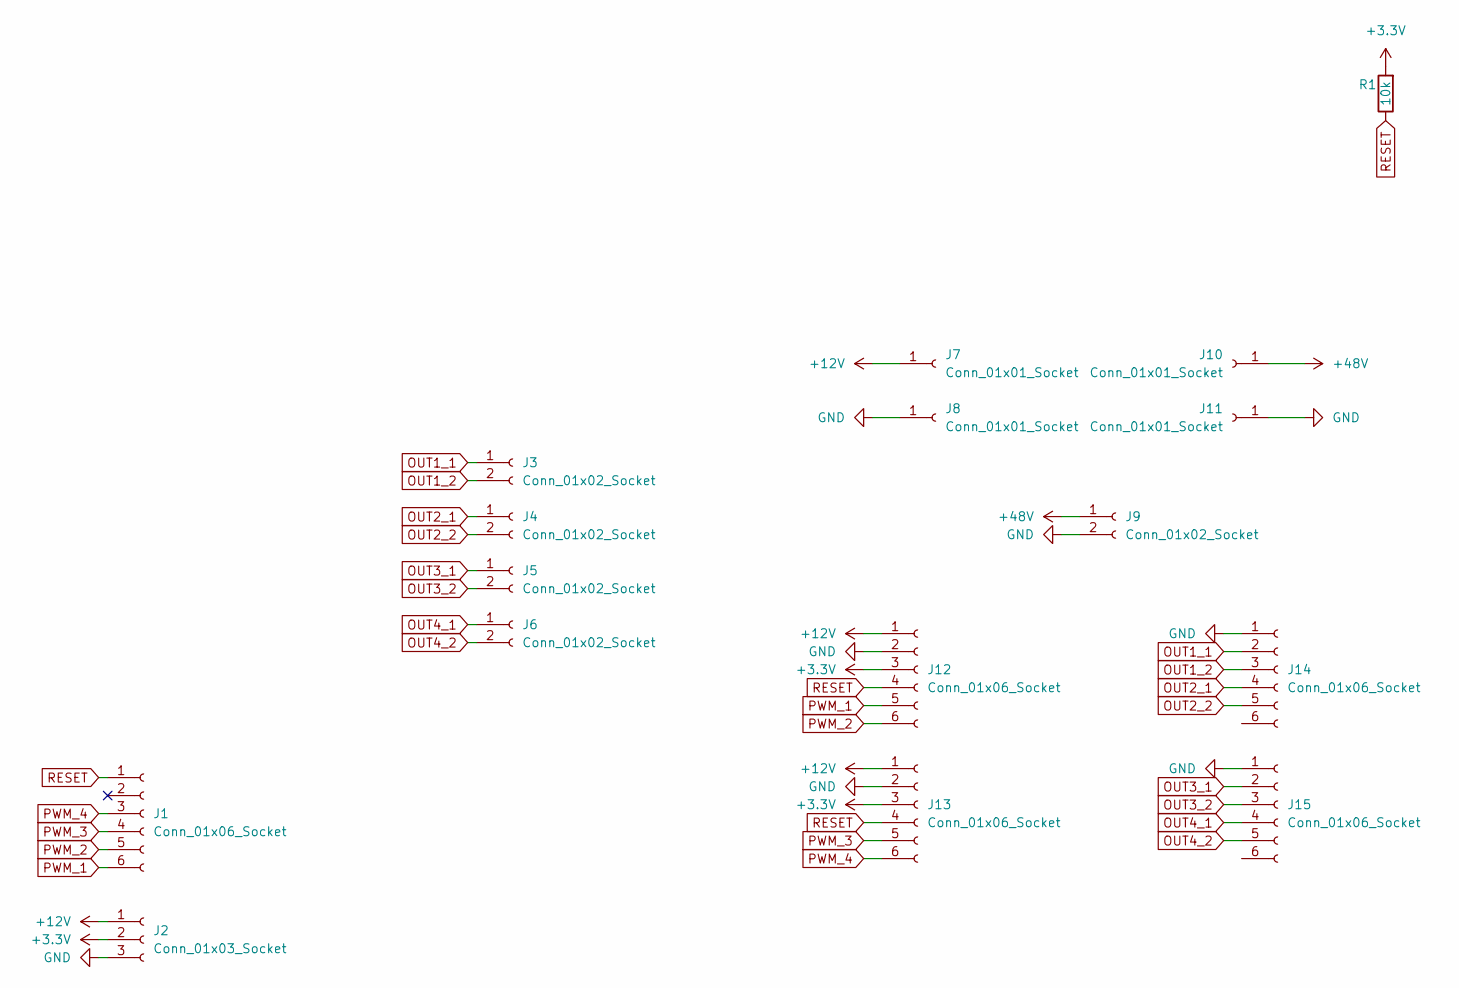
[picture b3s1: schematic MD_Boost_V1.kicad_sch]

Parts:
J1: Conn_01x06_Socket; TE_84952-6_1x06-1MP_P1.0mm_Horizontal
J2: Conn_01x03_Socket; JST_XH_B3B-XH-AM_1x03_P2.50mm_Vertical
J3, J4, J5, J6: Conn_01x02_Socket; JST_XH_B2B-XH-A_1x02_P2.50mm_Vertical
J7, J8, J10, J11: Conn_01x01_Socket; PinSocket_1x01_P2.54mm_Vertical
J9: Conn_01x02_Socket; JST_XH_B2B-XH-AM_1x02_P2.50mm_Vertical
J12, J13, J14, J15: Conn_01x06_Socket; PinSocket_1x06_P2.54mm_Vertical
R1: 10k; R_Axial_DIN0207_L6.3mm_D2.5mm_P10.16mm_Horizontal; LCSC C15401

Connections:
+3.3V: J2.2, J12.3, J13.3, R1.2
+12V: J2.1, J7.1, J12.1, J13.1
+48V: J9.1, J10.1
GND: J2.3, J8.1, J9.2, J11.1, J12.2, J13.2, J14.1, J15.1
OUT1_1: J3.1, J14.2
OUT1_2: J3.2, J14.3
OUT2_1: J4.1, J14.4
OUT2_2: J4.2, J14.5
OUT3_1: J5.1, J15.2
OUT3_2: J5.2, J15.3
OUT4_1: J6.1, J15.4
OUT4_2: J6.2, J15.5
PWM_1: J1.6, J12.5
PWM_2: J1.5, J12.6
PWM_3: J1.4, J13.5
PWM_4: J1.3, J13.6
RESET: J1.1, J12.4, J13.4, R1.1

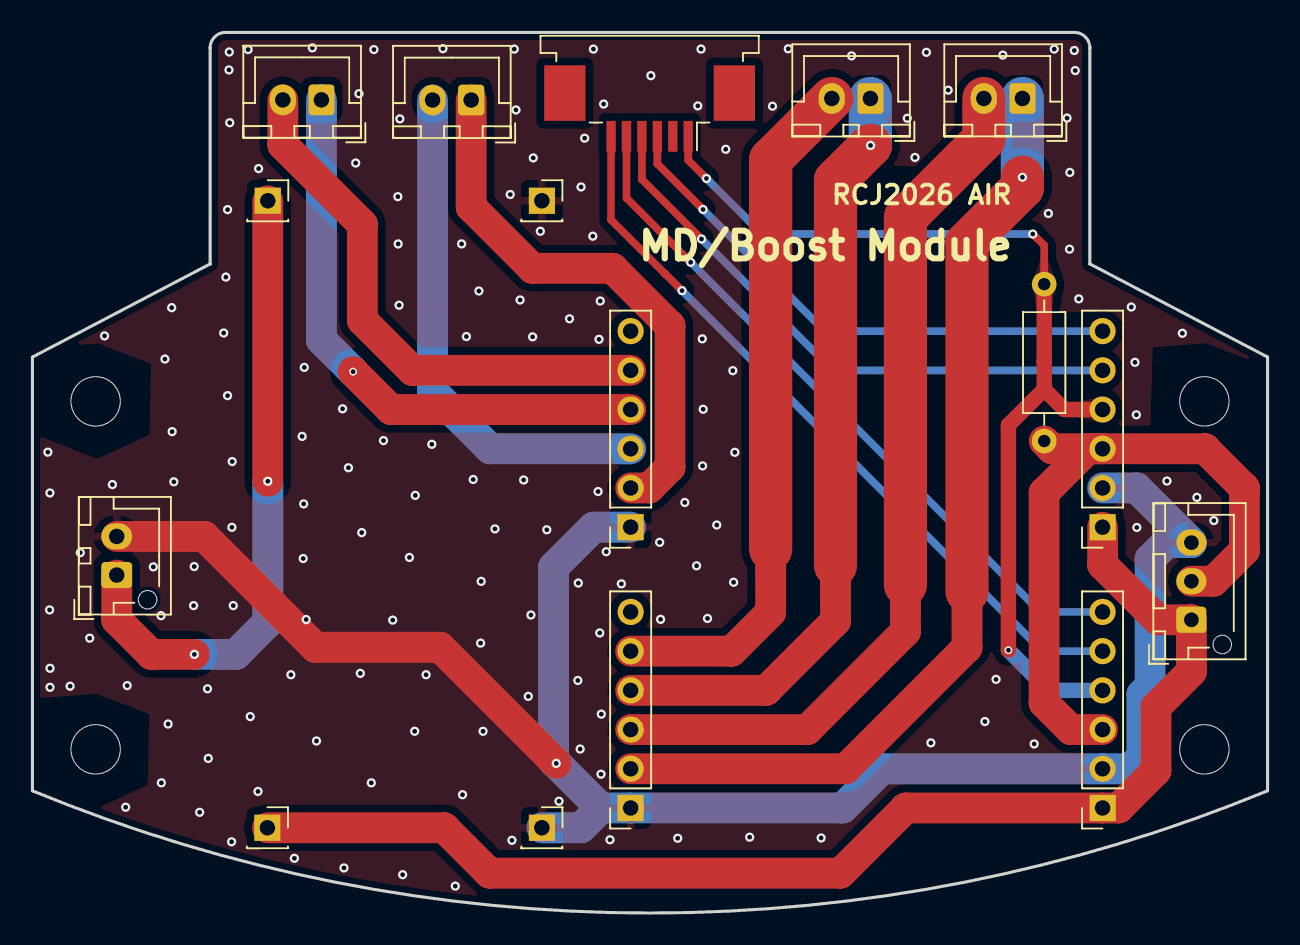
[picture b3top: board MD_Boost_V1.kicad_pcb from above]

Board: 2 copper layers, 80.0 x 57.0 mm, 20 parts (0 on the bottom side), 17 nets.

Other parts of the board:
H3, H3#2, H4, H4#2: MountingHole; MountingHole_3.2mm_M3
